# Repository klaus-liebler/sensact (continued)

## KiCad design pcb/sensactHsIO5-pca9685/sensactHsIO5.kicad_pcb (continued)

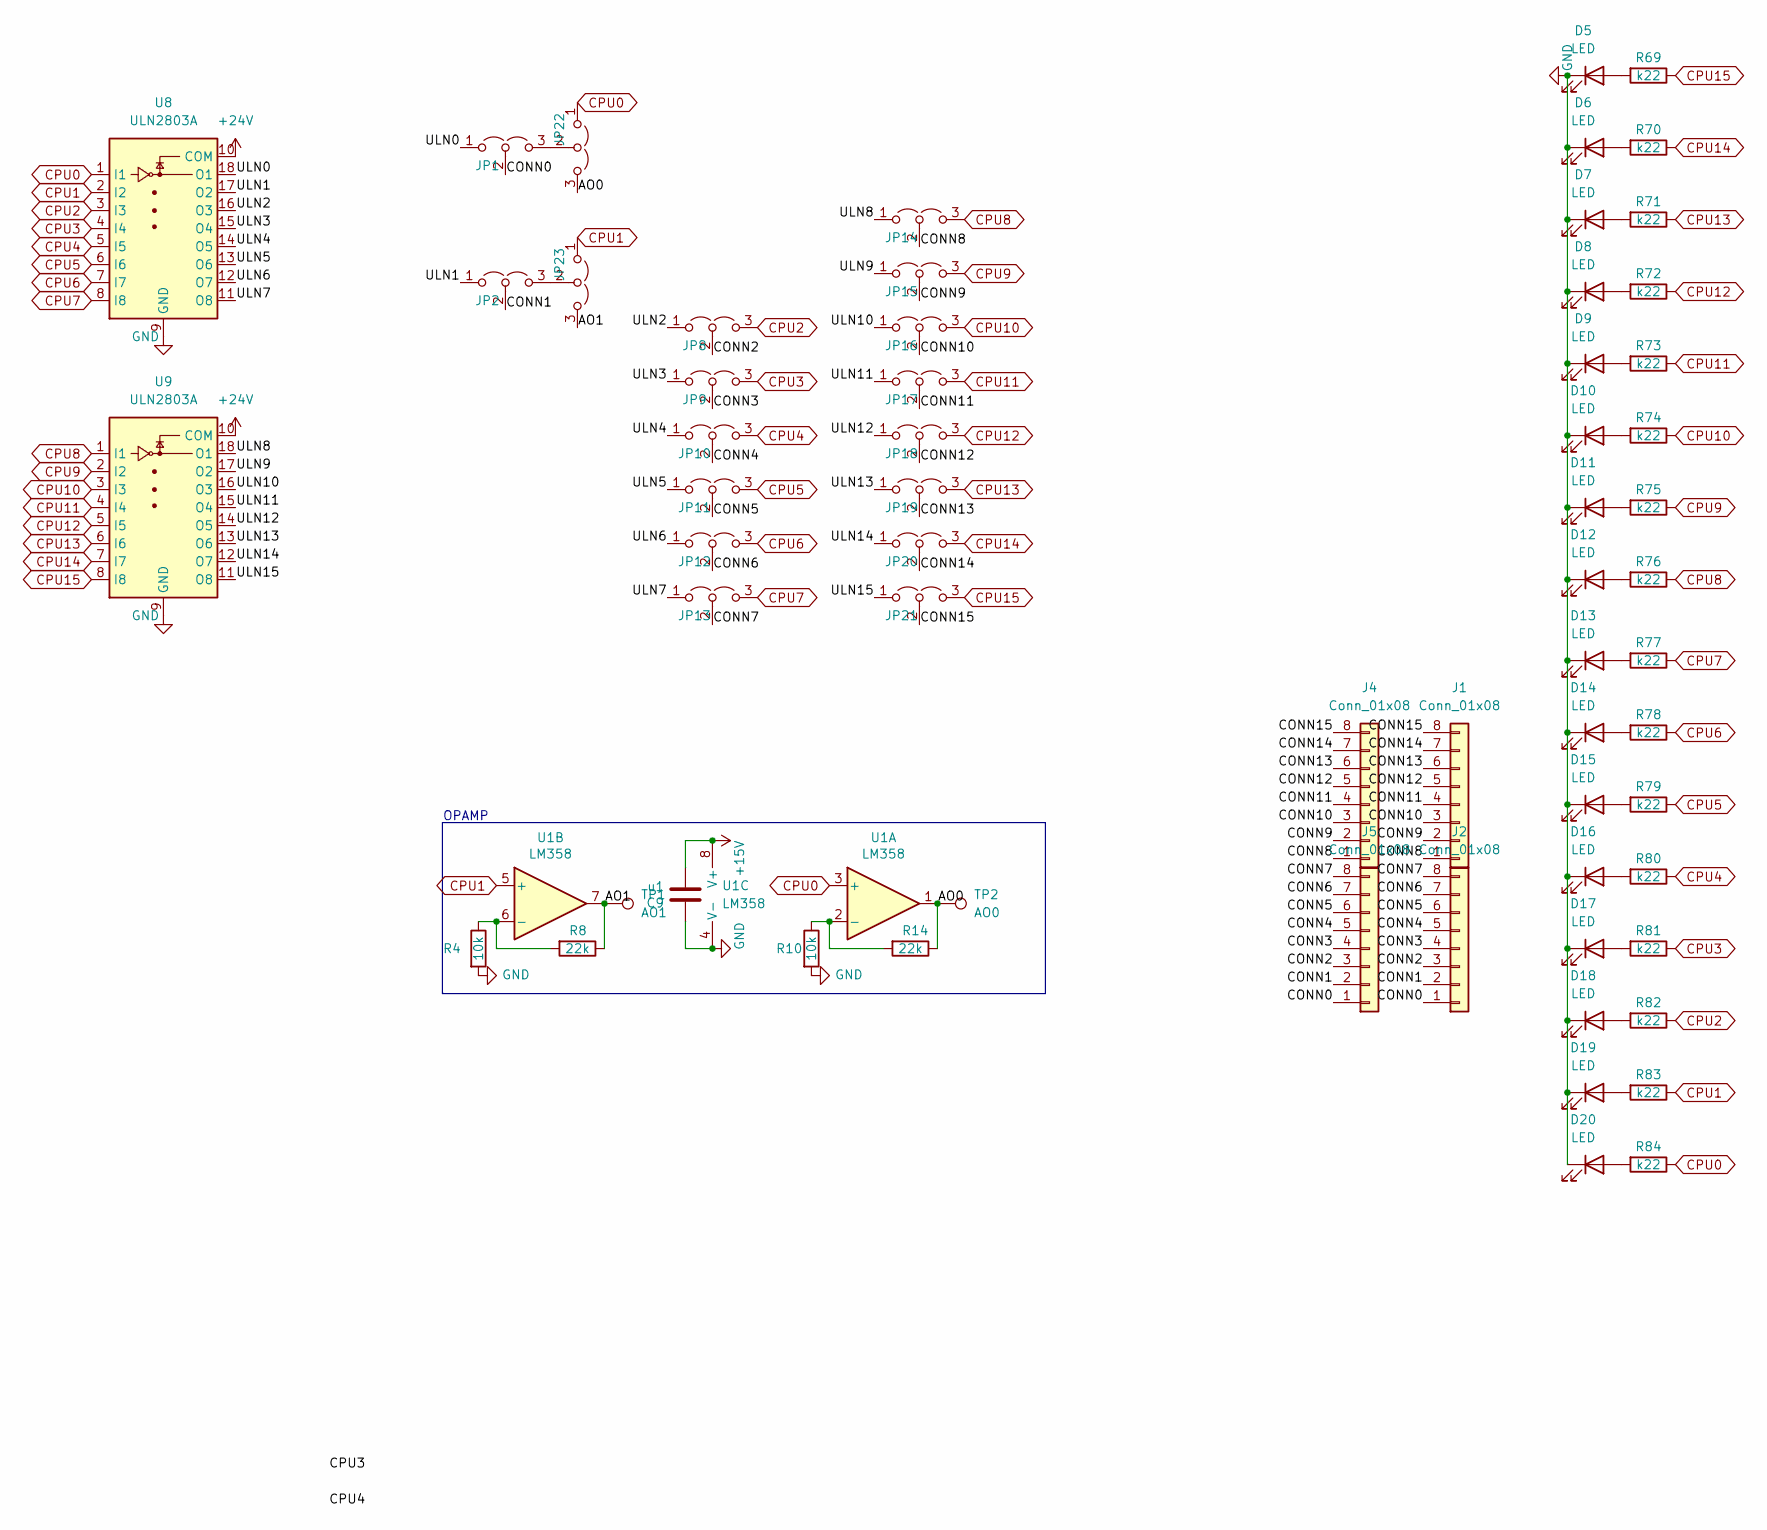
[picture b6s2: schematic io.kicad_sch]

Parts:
C9: u1; C_0402_1005Metric
D5, D6, D7, D8, D9, D10, D11, D12, D13, D14, D15, D16, D17, D18, D19, D20: LED; LED_1606
J1, J2: Conn_01x08; PhoenixContact_MC_0,5_8-G-2.5_1x08_P2.50mm_Horizontal
J4, J5: Conn_01x08; KF141R-8p
JP1, JP2, JP8, JP9, JP10, JP11, JP12, JP13, JP14, JP15, JP16, JP17, JP18, JP19, JP20, JP21, JP22, JP23: ULN_CPU; SolderJumper-3_P1.3mm_Open_RoundedPad1.0x1.5mm
R4, R10: 10k; R_0402_1005Metric
R8, R14: 22k; R_0402_1005Metric
R69, R70, R71, R72, R73, R74, R75, R76, R77, R78, R79, R80, R81, R82, R83, R84: k22; R_0402_1005Metric
TP1: AO1; TestPoint_Pad_2.0x2.0mm
TP2: AO0; TestPoint_Pad_2.0x2.0mm
U1: LM358
U8, U9: ULN2803A; SOIC-18W_7.5x11.6mm_P1.27mm

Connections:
+15V: C9.2, U1.8 (V+); also elsewhere on the board
/io/AO0: JP22.3 (B), R14.1, TP2.1, U1.1
/io/AO1: JP23.3 (B), R8.1, TP1.1, U1.7
/io/CONN0: J2.1, J5.1, JP1.2 (C)
/io/CONN1: J2.2, J5.2, JP2.2 (C)
/io/CONN2: J2.3, J5.3, JP8.2 (C)
/io/CONN3: J2.4, J5.4, JP9.2 (C)
/io/CONN4: J2.5, J5.5, JP10.2 (C)
/io/CONN5: J2.6, J5.6, JP11.2 (C)
/io/CONN6: J2.7, J5.7, JP12.2 (C)
/io/CONN7: J2.8, J5.8, JP13.2 (C)
/io/ULN0: JP1.1 (A), U8.18 (O1)
/io/ULN1: JP2.1 (A), U8.17 (O2)
/io/ULN2: JP8.1 (A), U8.16 (O3)
/io/ULN3: JP9.1 (A), U8.15 (O4)
/io/ULN4: JP10.1 (A), U8.14 (O5)
/io/ULN5: JP11.1 (A), U8.13 (O6)
/io/ULN6: JP12.1 (A), U8.12 (O7)
/io/ULN7: JP13.1 (A), U8.11 (O8)
/io/ULN8: JP14.1 (A), U9.18 (O1)
/io/ULN9: JP15.1 (A), U9.17 (O2)
/io/ULN10: JP16.1 (A), U9.16 (O3)
/io/ULN11: JP17.1 (A), U9.15 (O4)
/io/ULN12: JP18.1 (A), U9.14 (O5)
/io/ULN13: JP19.1 (A), U9.13 (O6)
/io/ULN14: JP20.1 (A), U9.12 (O7)
/io/ULN15: JP21.1 (A), U9.11 (O8)
CPU0: JP22.1 (A), R84.1, U1.3 (+), U8.1 (I1); also elsewhere on the board
CPU1: JP23.1 (A), R83.1, U1.5 (+), U8.2 (I2); also elsewhere on the board
CPU2: JP8.3 (B), R82.1, U8.3 (I3); also elsewhere on the board
CPU3: JP9.3 (B), R81.1, U8.4 (I4); also elsewhere on the board
CPU4: JP10.3 (B), R80.1, U8.5 (I5); also elsewhere on the board
CPU5: JP11.3 (B), R79.1, U8.6 (I6); also elsewhere on the board
CPU6: JP12.3 (B), R78.1, U8.7 (I7); also elsewhere on the board
CPU7: JP13.3 (B), R77.1, U8.8 (I8); also elsewhere on the board
CPU8: JP14.3 (B), R76.1, U9.1 (I1); also elsewhere on the board
CPU9: JP15.3 (B), R75.1, U9.2 (I2); also elsewhere on the board
CPU10: JP16.3 (B), R74.1, U9.3 (I3); also elsewhere on the board
CPU11: JP17.3 (B), R73.1, U9.4 (I4); also elsewhere on the board
CPU12: JP18.3 (B), R72.1, U9.5 (I5); also elsewhere on the board
CPU13: JP19.3 (B), R71.1, U9.6 (I6); also elsewhere on the board
CPU14: JP20.3 (B), R70.1, U9.7 (I7); also elsewhere on the board
CPU15: JP21.3 (B), R69.1, U9.8 (I8); also elsewhere on the board
unnamed: D5.2 (A), R69.2
unnamed: D6.2 (A), R70.2
unnamed: D7.2 (A), R71.2
unnamed: D8.2 (A), R72.2
unnamed: D9.2 (A), R73.2
unnamed: D10.2 (A), R74.2
unnamed: D11.2 (A), R75.2
unnamed: D12.2 (A), R76.2
unnamed: D13.2 (A), R77.2
unnamed: D14.2 (A), R78.2
unnamed: D15.2 (A), R79.2
unnamed: D16.2 (A), R80.2
unnamed: D17.2 (A), R81.2
unnamed: D18.2 (A), R82.2
unnamed: D19.2 (A), R83.2
unnamed: D20.2 (A), R84.2
unnamed: JP1.3 (B), JP22.2 (C)
unnamed: JP2.3 (B), JP23.2 (C)
unnamed: R10.1, R14.2, U1.2 (-)
unnamed: R4.1, R8.2, U1.6 (-)

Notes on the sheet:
OPAMP

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
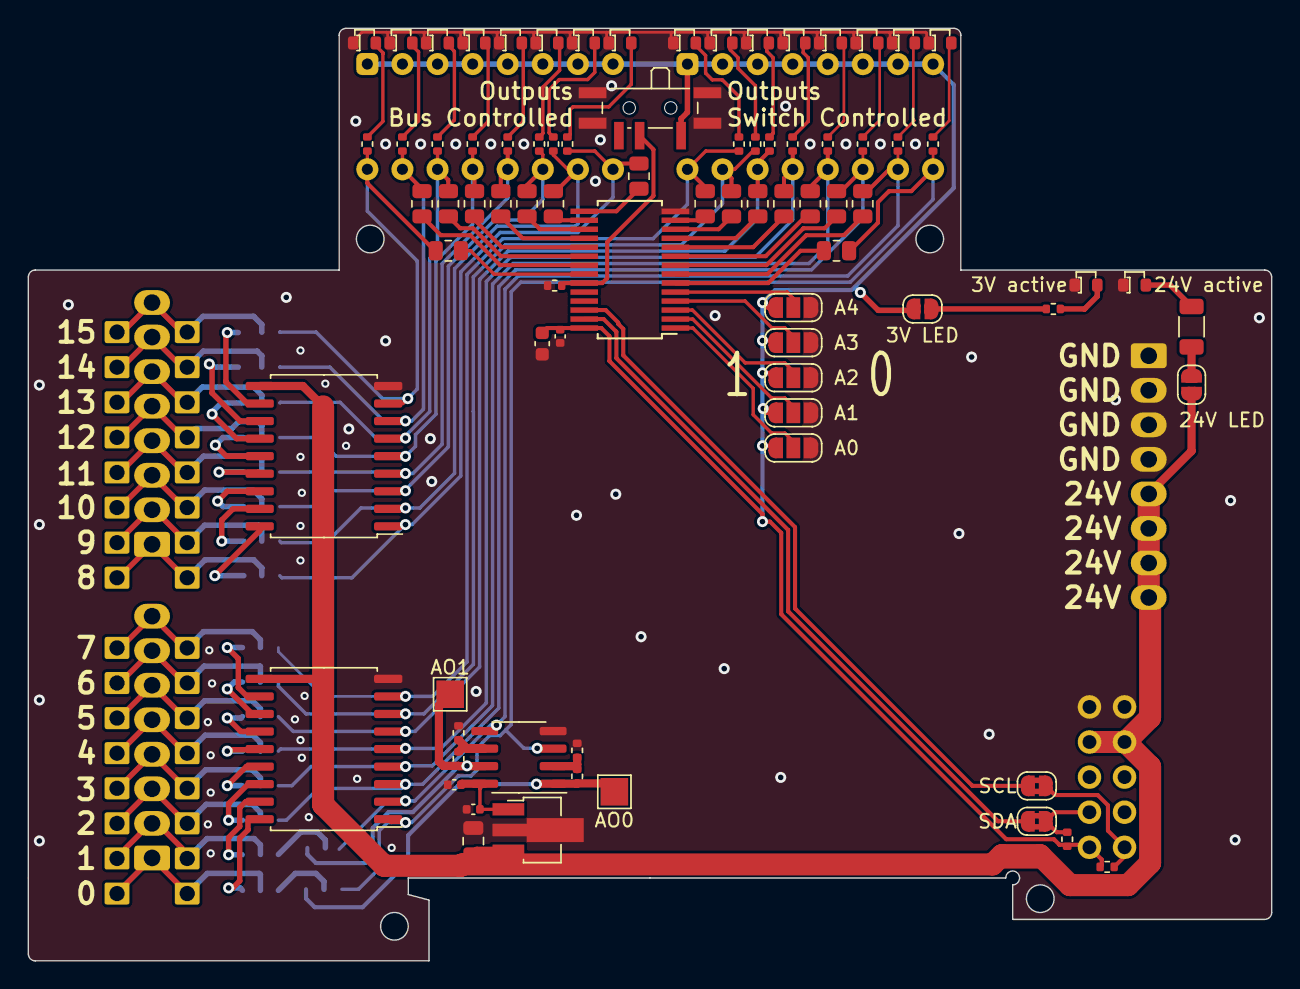
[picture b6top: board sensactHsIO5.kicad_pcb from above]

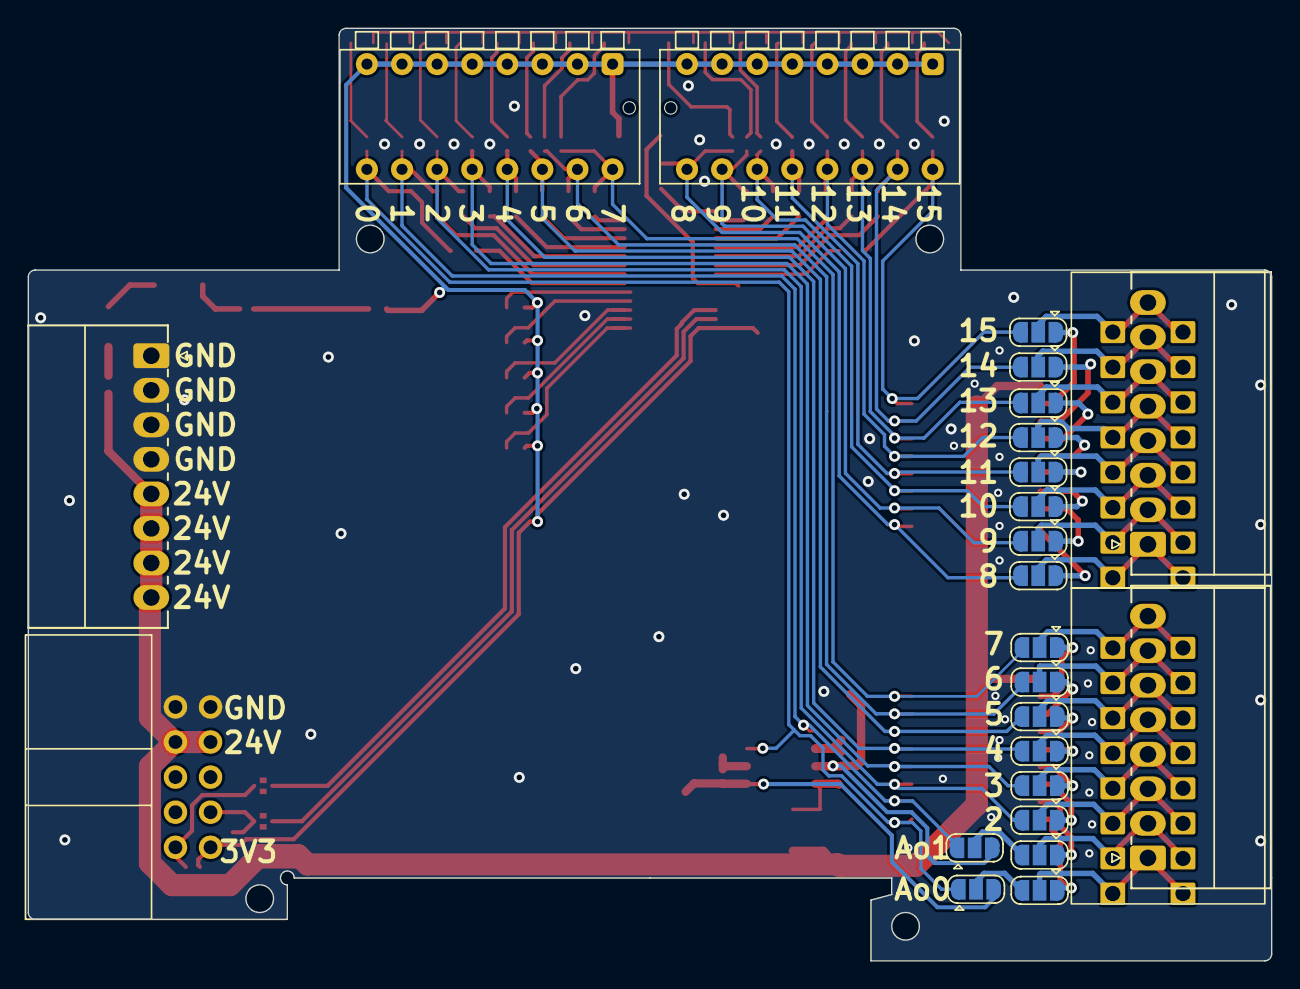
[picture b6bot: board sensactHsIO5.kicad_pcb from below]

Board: 2 copper layers, 90.0 x 67.5 mm, 107 parts (26 on the bottom side), 104 nets.

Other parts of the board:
J3: Conn_01x08; PhoenixContact_MC_0,5_8-G-2.5_1x08_P2.50mm_Horizontal

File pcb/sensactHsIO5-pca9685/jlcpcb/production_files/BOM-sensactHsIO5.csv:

Comment,Designator,Footprint,LCSC
u47,C8,C_0805_2012Metric,C13967
u1,"C11,C2,C9",C_0402_1005Metric,C1525
K15,"R12,R13,R15,R16,R17,R18,R19,R21,R22,R23,R24,R25,R3,R5,R6,R9",R_0805_2012Metric,C17471
4k7,R11,R_1206_3216Metric,C17936
ULN2803A,"U8,U9",SOIC-18W_7.5x11.6mm_P1.27mm,C181731
k22,"R20,R69,R70,R71,R72,R73,R74,R75,R76,R77,R78,R79,R80,R81,R82,R83,R84",R_0402_1005Metric,C25091
10k,"R10,R4",R_0402_1005Metric,C25744
22k,"R14,R8",R_0402_1005Metric,C25768
4k7,R7,R_0402_1005Metric,C25900
PCA9685PW,U3,TSSOP-28_4.4x9.7mm_Pitch0.65mm_handsolder,C2678753
22u,C7,C_0603_1608Metric,C59461
LM358,U1,SOIC-8_3.9x4.9mm_P1.27mm,C7950
24V active,"D1,D10,D11,D12,D13,D14,D15,D16,D17,D18,D19,D2,D20,D5,D6,D7,D8,D9",LED_1606,C965863
AO1,TP1,TestPoint_Pad_2.0x2.0mm,
4k7opt,R1,R_0402_1005Metric,
SCL,JP33,SolderJumper-2_P1.3mm_Bridged2Bar_RoundedPad1.0x1.5mm,
A4,JP7,SolderJumper-3_P1.3mm_Open_RoundedPad1.0x1.5mm_NumberLabels,
L78L15_SOT89,U4,SOT-89-3_Handsoldering,
A1,JP4,SolderJumper-3_P1.3mm_Open_RoundedPad1.0x1.5mm_NumberLabels,
4k7opt,R2,R_0402_1005Metric,
A0,JP3,SolderJumper-3_P1.3mm_Open_RoundedPad1.0x1.5mm_NumberLabels,
24V LED,JP24,SolderJumper-2_P1.3mm_Open_RoundedPad1.0x1.5mm,
SDA,JP34,SolderJumper-2_P1.3mm_Bridged2Bar_RoundedPad1.0x1.5mm,
A3,JP6,SolderJumper-3_P1.3mm_Open_RoundedPad1.0x1.5mm_NumberLabels,
A2,JP5,SolderJumper-3_P1.3mm_Open_RoundedPad1.0x1.5mm_NumberLabels,
3V LED,JP25,SolderJumper-2_P1.3mm_Open_RoundedPad1.0x1.5mm,
Auto Manu,SW7,SW_SPDT_PCM12_handsolder,
AO0,TP2,TestPoint_Pad_2.0x2.0mm,
ULN_CPU,JP8,SolderJumper-3_P1.3mm_Open_RoundedPad1.0x1.5mm,
ULN_CPU,JP16,SolderJumper-3_P1.3mm_Open_RoundedPad1.0x1.5mm,
ULN_CPU,JP11,SolderJumper-3_P1.3mm_Open_RoundedPad1.0x1.5mm,
ULN_CPU,JP10,SolderJumper-3_P1.3mm_Open_RoundedPad1.0x1.5mm,
ULN_CPU,JP18,SolderJumper-3_P1.3mm_Open_RoundedPad1.0x1.5mm,
SW_DIP_x08,SW5,SW_DIP_SPSTx08_Piano,
Conn_01x08,J4,KF141R-8p,
Bus,J8,IDC-Header_2x05_P2.54mm_Horizontal_tightCrtYd,
ULN_CPU,JP17,SolderJumper-3_P1.3mm_Open_RoundedPad1.0x1.5mm,
ULN_CPU,JP14,SolderJumper-3_P1.3mm_Open_RoundedPad1.0x1.5mm,
ULN_CPU,JP9,SolderJumper-3_P1.3mm_Open_RoundedPad1.0x1.5mm,
ULN_CPU,JP2,SolderJumper-3_P1.3mm_Open_RoundedPad1.0x1.5mm,
ULN_CPU,JP15,SolderJumper-3_P1.3mm_Open_RoundedPad1.0x1.5mm,
SW_DIP_x08,SW4,SW_DIP_SPSTx08_Piano,
ULN_CPU,JP20,SolderJumper-3_P1.3mm_Open_RoundedPad1.0x1.5mm,
ULN_CPU,JP19,SolderJumper-3_P1.3mm_Open_RoundedPad1.0x1.5mm,
ULN_CPU,JP13,SolderJumper-3_P1.3mm_Open_RoundedPad1.0x1.5mm,
ULN_CPU,JP1,SolderJumper-3_P1.3mm_Open_RoundedPad1.0x1.5mm,
Conn_01x08,J5,KF141R-8p,
ULN_CPU,JP21,SolderJumper-3_P1.3mm_Open_RoundedPad1.0x1.5mm,
ULN_CPU,JP12,SolderJumper-3_P1.3mm_Open_RoundedPad1.0x1.5mm,
ULN_CPU,JP22,SolderJumper-3_P1.3mm_Open_RoundedPad1.0x1.5mm,
ULN_CPU,JP23,SolderJumper-3_P1.3mm_Open_RoundedPad1.0x1.5mm,
Conn_01x08,J3,"PhoenixContact_MC_0,5_8-G-2.5_1x08_P2.50mm_Horizontal",
Conn_01x08,J1,"PhoenixContact_MC_0,5_8-G-2.5_1x08_P2.50mm_Horizontal",
Conn_01x08,J2,"PhoenixContact_MC_0,5_8-G-2.5_1x08_P2.50mm_Horizontal",
